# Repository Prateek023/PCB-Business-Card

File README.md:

# PCB Business Card Project

This project aims to create a unique PCB business card using a NFC technology.

## Features
- Slim and compact design
- LED lighting effects
- QR code integration for digital contact information

## Getting Started
To assemble the PCB business card, you will need the following components:
- Printed circuit board (included in the repository)
- Soldering iron and solder
- LEDs
- NT3H1101 -https://www.mouser.com/datasheet/2/302/NT3H1101_1201-1127167.pdf
- Resistors
- Capacitor

To assemble:
1. Solder the components onto the PCB following the provided schematic.

## Usage
Once assembled, the PCB business card can be used to share contact information in a unique and memorable way. Simply hand it to someone, and they can scan the QR code to save your contact details digitally.

##
Its hardware is not yet ready. Once we get the PCB after fabrication then we can write any Link to its NFC Chip using Mobile (NFC enabled).

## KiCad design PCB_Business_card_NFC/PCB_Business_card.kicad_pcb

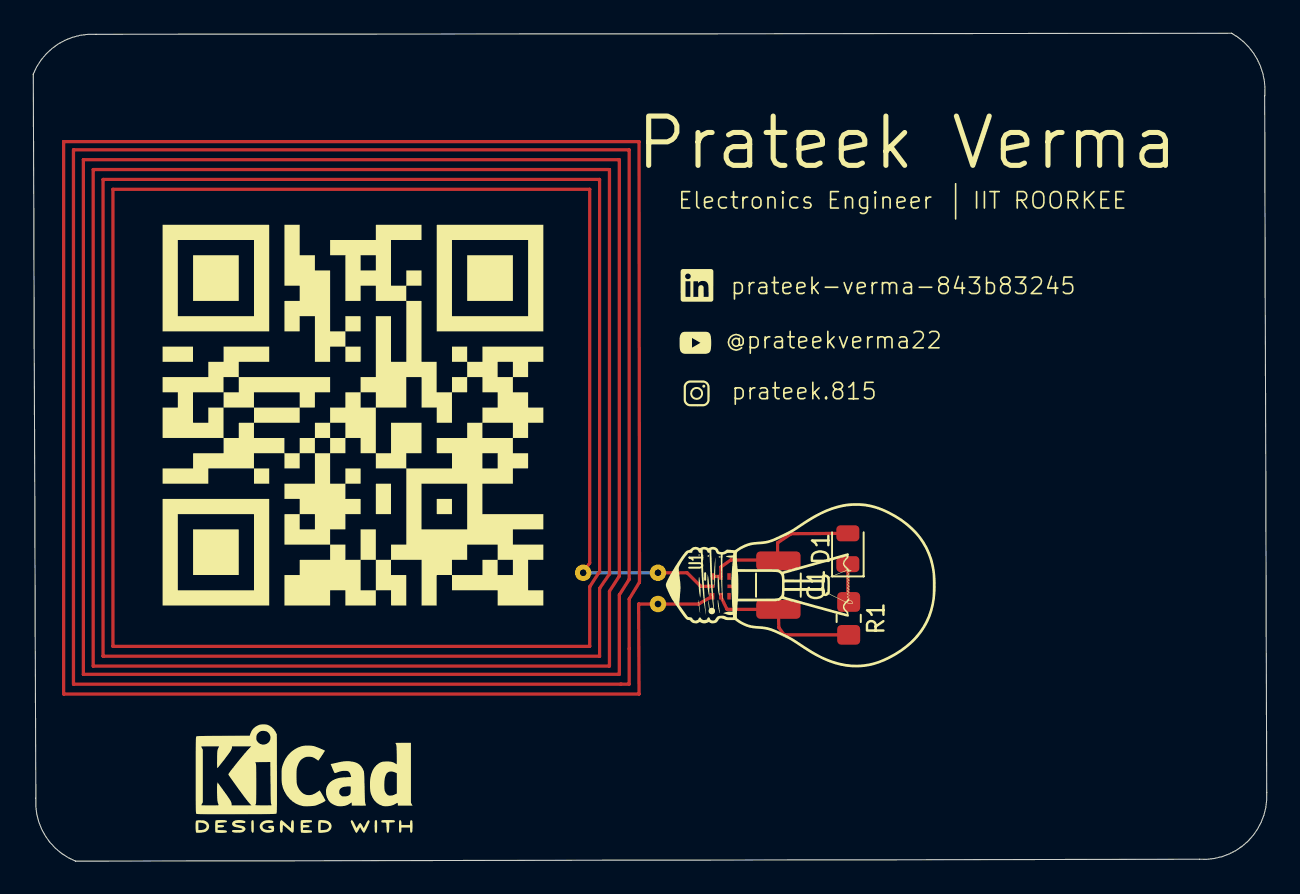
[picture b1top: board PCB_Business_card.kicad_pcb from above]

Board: 2 copper layers, 75.0 x 50.3 mm, 5 parts (0 on the bottom side), 3 nets, no tracks yet.

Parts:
C1: 220 nf; C_1210_3225Metric
D1: LED; LED_0805_2012Metric
R1: 47; R_0805_2012Metric_Pad1.20x1.40mm_HandSolder
U1: NT3H1101W0FHKH; IC_NT3H1101W0FHKH
g1: LOGO

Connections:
unnamed: C1.1, D1.2 (A), U1.6 (VCC), U1.7 (VOUT)
unnamed: D1.1 (K), R1.1
unnamed: C1.2, R1.2, U1.2 (VSS)

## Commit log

2024-06-03 Rename PCB_Business_card_NFC/Antenna design-backups/3D view.png to 3D view.png
2024-06-03 Rename PCB_Business_card_NFC/Antenna design-backups/PCB_layout.png to PCB_layout.png
2024-06-03 Rename PCB_Business_card_NFC/Antenna design-backups/Schematic.png to Schematic.png
